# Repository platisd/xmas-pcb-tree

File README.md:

# xmas-pcb-tree
The PCB design files and firmware for a xmas tree shaped PCB, using an ATTiny25 and MOSFETs to blink several LEDs - http://plat.is/xmaspcb

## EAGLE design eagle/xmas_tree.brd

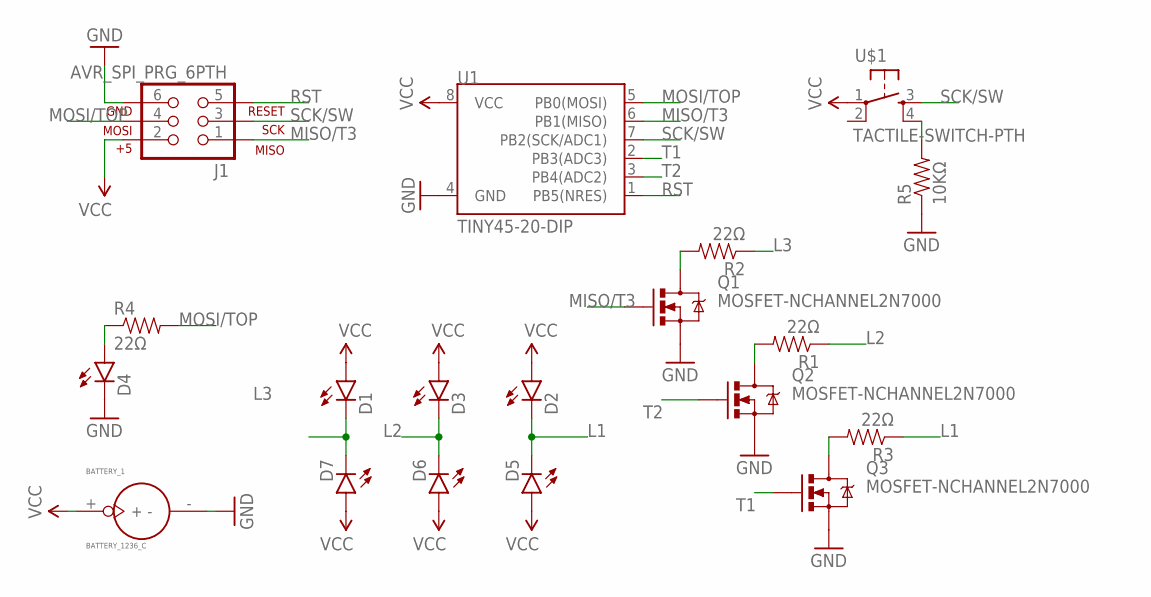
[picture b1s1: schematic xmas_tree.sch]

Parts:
BATTERY_1: BATTERY_1236_C
D1, D2, D3, D4, D5, D6, D7: LED; LED5MM-SLIM
J1: AVR_SPI_PRG_6PTH; 2X3
Q1, Q2, Q3: MOSFET-NCHANNEL2N7000; TO-92
R1, R2, R3, R4: 22Ω; 1206
R5: 10KΩ; 1206
U1: TINY45-20-DIP; DIP08
U$1: TACTILE-SWITCH-PTH; TAC-SWITCH-PTH

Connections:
GND: BATTERY_1.-, D4.K (C), J1.6, Q1.1 (S), Q2.1 (S), Q3.1 (S), R5.1, U1.4 (GND)
L1: D2.K (C), D5.K (C), R3.1
L2: D3.K (C), D6.K (C), R1.1
L3: D1.K (C), D7.K (C), R2.1
MISO/T3: J1.1, Q1.2 (G), U1.6 (PB1(MISO))
MOSI/TOP: J1.4, R4.2, U1.5 (PB0(MOSI))
unnamed: Q1.3 (D), R2.2
unnamed: R5.2, U$1.4
unnamed: Q2.3 (D), R1.2
unnamed: Q3.3 (D), R3.2
unnamed: D4.A, R4.1
RST: J1.5, U1.1 (PB5(NRES))
SCK/SW: J1.3, U1.7 (PB2(SCK/ADC1)), U$1.3
T1: Q3.2 (G), U1.2 (PB3(ADC3))
T2: Q2.2 (G), U1.3 (PB4(ADC2))
VCC: BATTERY_1.+, D1.A, D2.A, D3.A, D5.A, D6.A, D7.A, J1.2, U1.8 (VCC), U$1.1

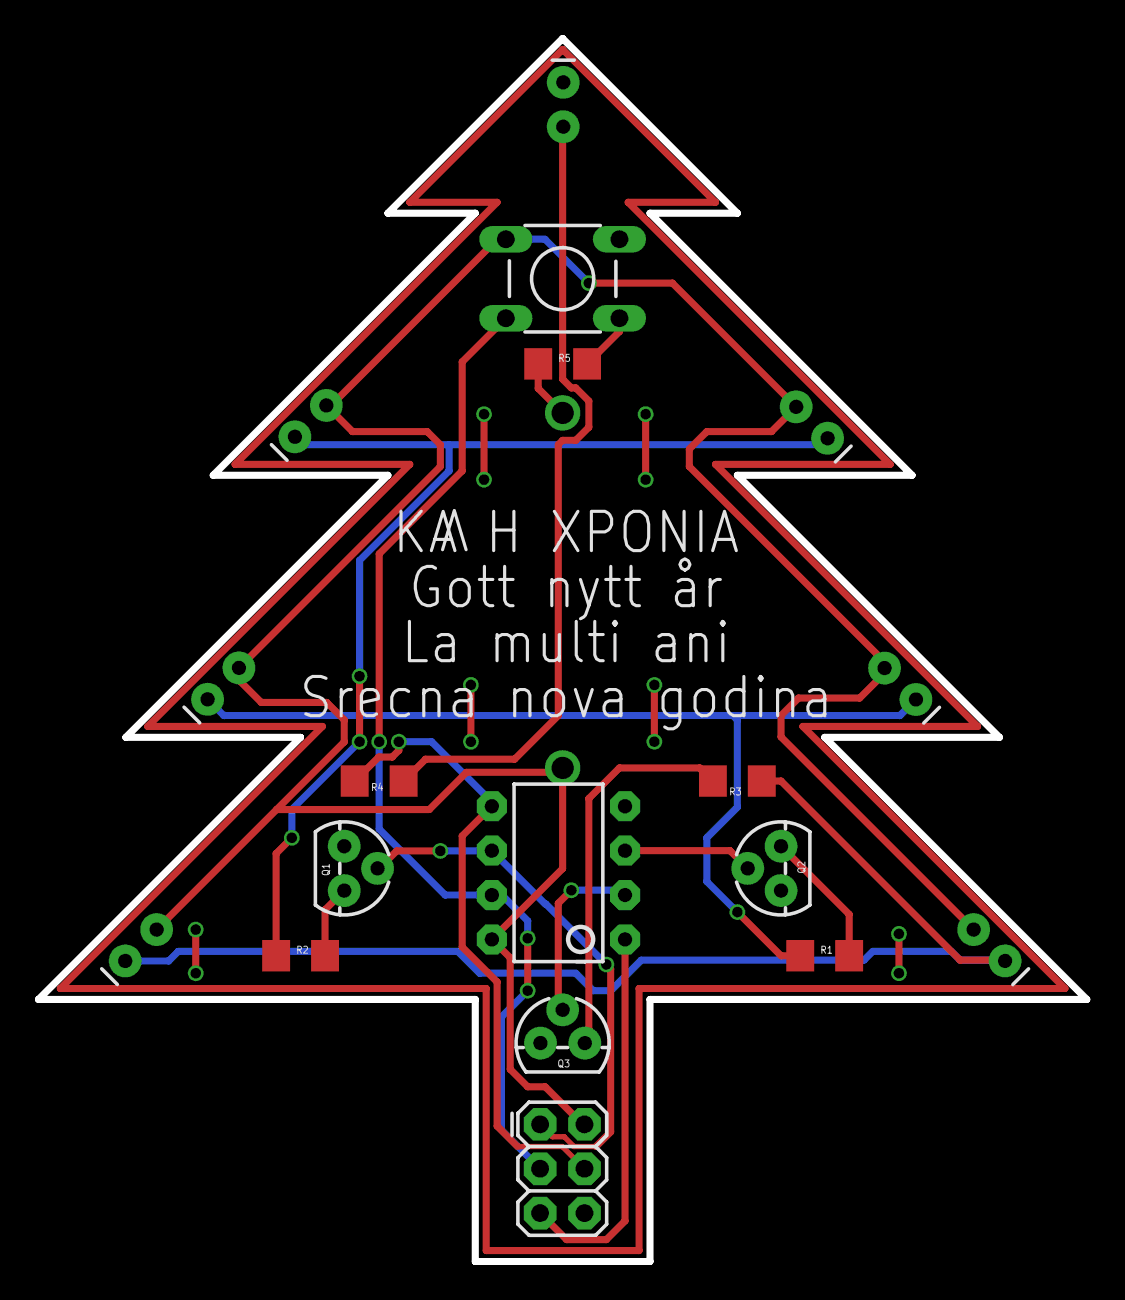
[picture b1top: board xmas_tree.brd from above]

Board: 2 copper layers, 60.0 x 70.0 mm, 19 parts (1 on the bottom side), 16 nets.

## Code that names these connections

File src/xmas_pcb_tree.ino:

/**
   Xmas PCB Tree
   The ATtiny 25/45/85 microcontroller will be sleeping until a button is pressed.

   More info at: http://plat.is/xmaspcb
   Most code is based on Nick Gammon's example: http://www.gammon.com.au/forum/?id=11488&reply=9#reply9
*/

#include <avr/sleep.h>    // Sleep Modes
#include <avr/power.h>    // Power management

const int ledPins[4] = {PB0, PB1, PB4, PB3};
const int switchPin = PB2;
const int numOfSequences = 5; // How many different sequences we have
int currentSeq = 0;

ISR (PCINT0_vect)
{
  // We leave this blank as we don't want to do anything specific in the interrupt, just wake the mcu up
}

void setup() {
  for (int i = 0; i < 4; i++) {
    pinMode(ledPins[i], OUTPUT);
  }
  pinMode(switchPin, INPUT);
  // pin change interrupt for D2
  PCMSK  |= bit (PCINT2);  // want pin D2 (PB2)
  GIFR   |= bit (PCIF);    // clear any outstanding interrupts
  GIMSK  |= bit (PCIE);    // enable pin change interrupts
}

void loop() {
  goToSleep(); // Sleep until the button at PB2 is pressed
  lightSequence();
}

void goToSleep() {
  set_sleep_mode(SLEEP_MODE_PWR_DOWN);
  ADCSRA = 0;            // turn off ADC
  power_all_disable ();  // power off ADC, Timer 0 and 1, serial interface
  sleep_enable();
  sleep_cpu();          // Sleep here and wait for the interrupt
  sleep_disable();
  power_all_enable();    // power everything back on
}

void lightSequence() {
  currentSeq = (currentSeq + 1) % numOfSequences;
  switch (currentSeq) {
    case 0:
      blinking1(100);
      break;
    case 1:
      blinking1(40);
      blinking1(40);
      break;
    case 2:
      blinking2();
      delay(50);
      blinking2();
      break;
    case 3:
      blinking3();
      delay(100);
      blinking3();
      break;
    case 4:
      blinking4(100);
      break;
    default:
      break;
  }
}

void blinking1(int blinkingDelay) {
  for (int i = 0; i < 4; i++) {
    digitalWrite(ledPins[i], HIGH);
    delay(blinkingDelay);
    digitalWrite(ledPins[i], LOW);
    delay(blinkingDelay);
  }
  for (int i = 3; i >= 0; i--) {
    digitalWrite(ledPins[i], HIGH);
    delay(blinkingDelay);
    digitalWrite(ledPins[i], LOW);
    delay(blinkingDelay);
  }
}

void blinking2() {
  digitalWrite(ledPins[0], HIGH);
  delay(100);
  digitalWrite(ledPins[0], LOW);
  for (int i = 3; i >= 1; i--) {
    digitalWrite(ledPins[i], HIGH);
    delay(200);
    digitalWrite(ledPins[i], LOW);
    delay(100);
  }
}

void blinking3() {
  digitalWrite(ledPins[3], HIGH);
  delay(100);
  digitalWrite(ledPins[3], LOW);
  digitalWrite(ledPins[1], HIGH);
  delay(100);
  digitalWrite(ledPins[1], LOW);
  digitalWrite(ledPins[2], HIGH);
  delay(100);
  digitalWrite(ledPins[2], LOW);
  digitalWrite(ledPins[0], HIGH);
  delay(100);
  digitalWrite(ledPins[0], LOW);
}

void blinking4(int blinkingDelay) {
  for (int i = 3; i >= 0; i--) {
    digitalWrite(ledPins[i], HIGH);
    delay(blinkingDelay);
    digitalWrite(ledPins[i], LOW);
    delay(blinkingDelay);
  }
  for (int i = 0; i < 4; i++) {
    digitalWrite(ledPins[i], HIGH);
    delay(blinkingDelay);
    digitalWrite(ledPins[i], LOW);
    delay(blinkingDelay);
  }
}

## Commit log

2016-12-13 Eagle Files rev. 0
2016-12-13 The sketch running on the ATtiny25
2016-12-13 3D printable snowflake as base
2016-12-17 More light sequences

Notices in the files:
parts and their libraries:
SparkFun-LED: Licensing: Creative Commons ShareAlike 4.0 International - https://creativecommons.org/licenses/by-sa/4.0
